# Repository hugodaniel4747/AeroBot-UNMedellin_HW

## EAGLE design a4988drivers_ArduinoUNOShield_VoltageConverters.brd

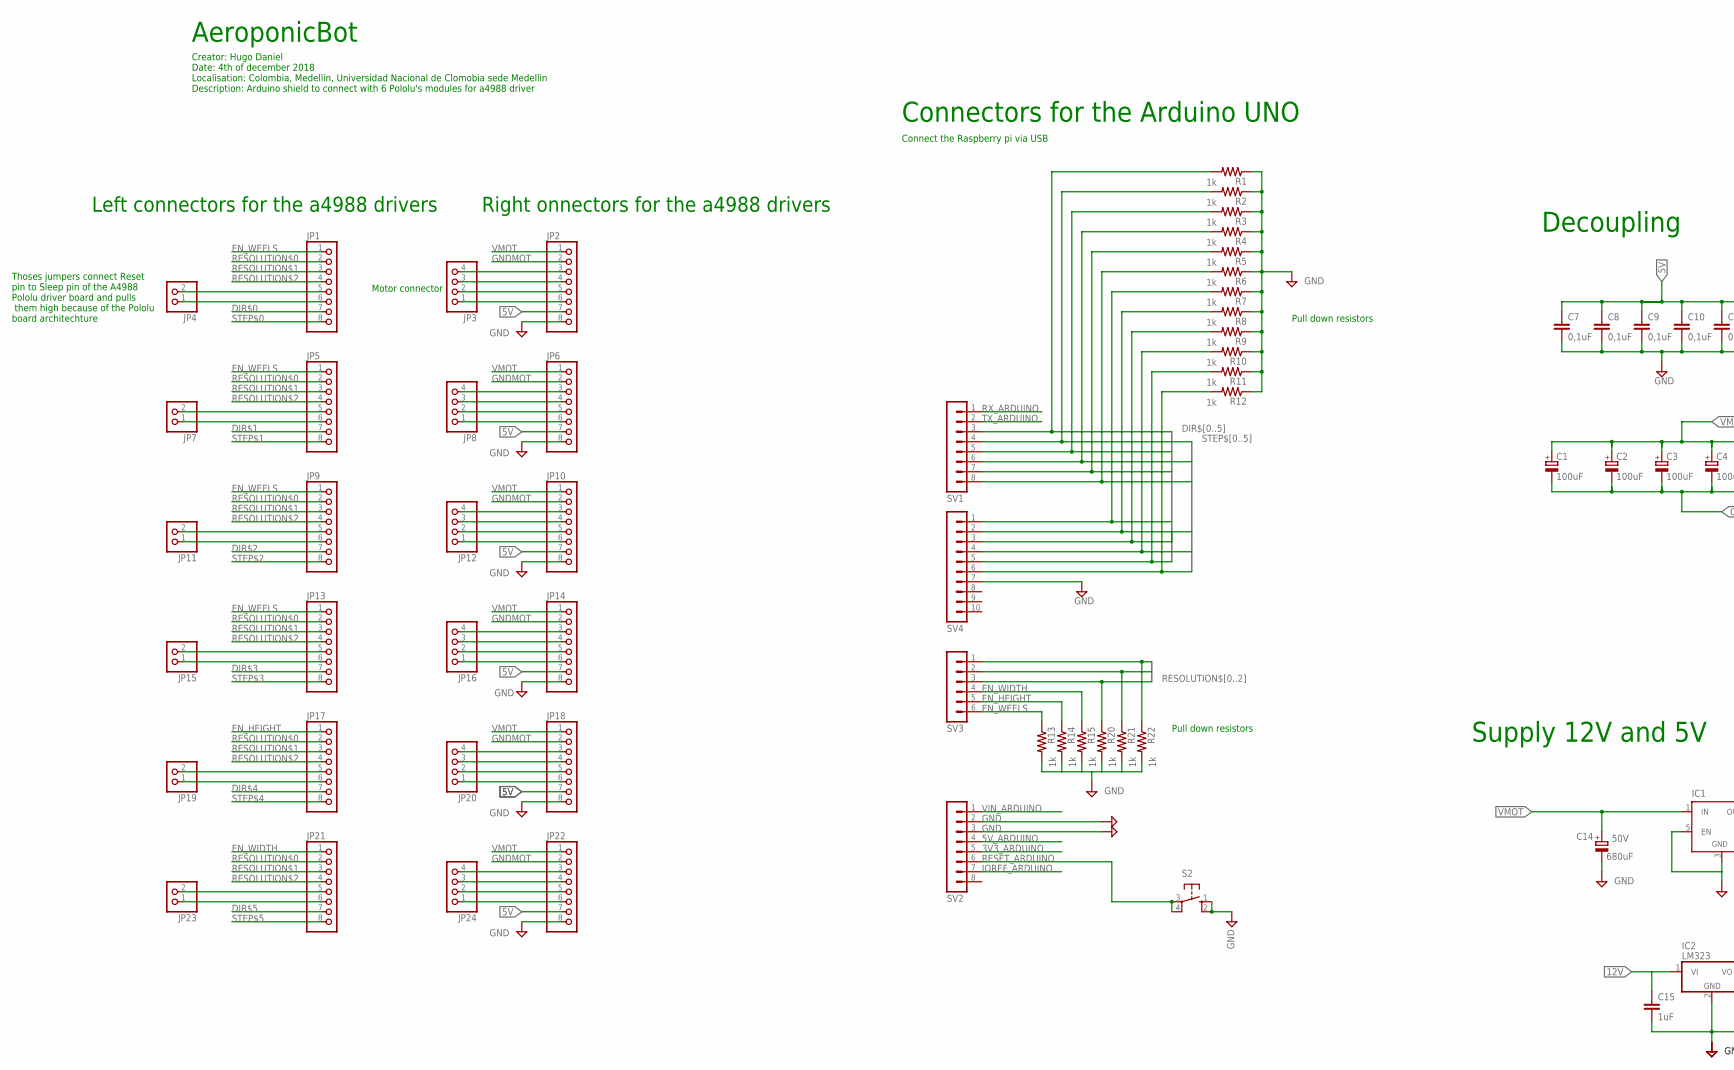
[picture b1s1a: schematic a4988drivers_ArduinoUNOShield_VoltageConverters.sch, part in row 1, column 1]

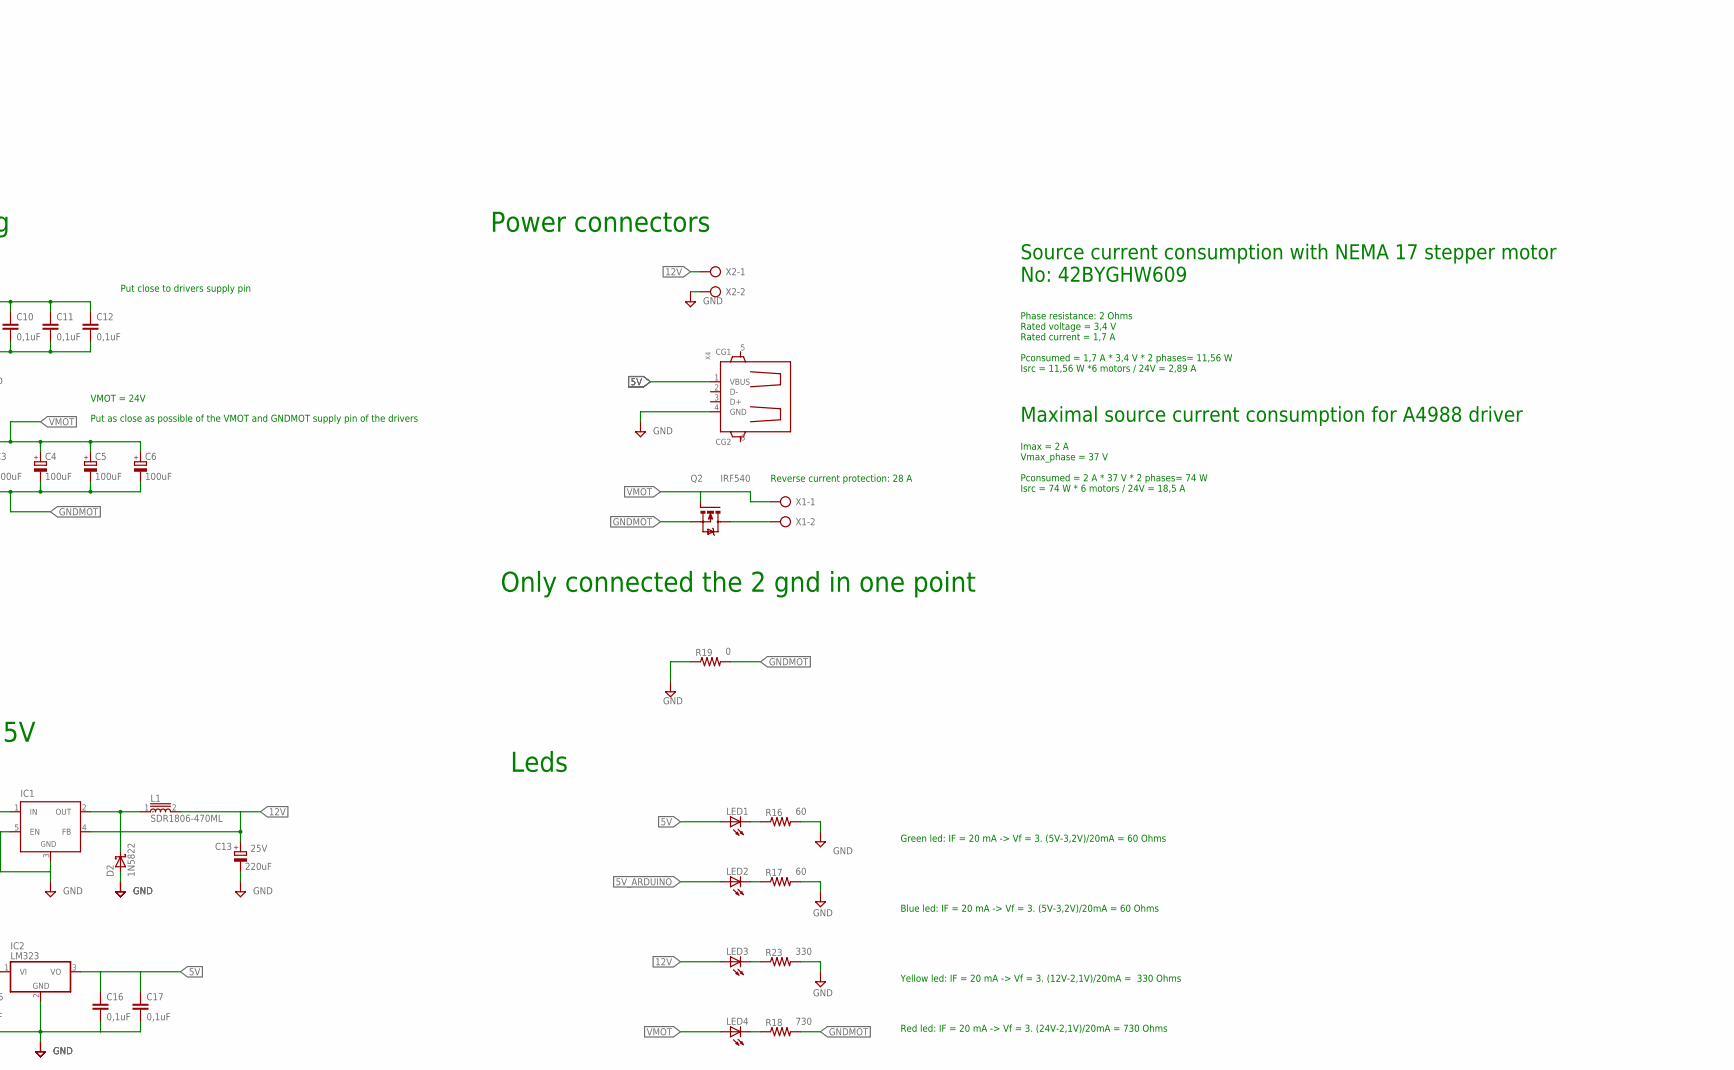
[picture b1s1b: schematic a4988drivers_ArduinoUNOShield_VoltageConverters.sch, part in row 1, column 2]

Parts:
C1, C2, C3, C4, C5, C6: 100uF; E5-10,5
C7, C8, C9, C10, C11, C12, C16, C17: 0,1uF; C050-030X075
C13: 220uF; E5-10,5
C14: 680uF; E5-10,5
C15: 1uF; C050-030X075
D2: 1N5822; DIOAD2120W130L950D530P
IC1: LM2596TV; TO220-51
IC2: LM323; TO220V
JP1, JP2, JP5, JP6, JP9, JP10, JP13, JP14, JP17, JP18, JP21, JP22: PINHD-1X8; 1X08
JP3, JP8, JP12, JP16, JP20, JP24: PINHD-1X4; 1X04
JP4, JP7, JP11, JP15, JP19, JP23: PINHD-1X2; 1X02
L1: SDR1806-470ML; INDP1830X1400X690L250X260N
LED1, LED2, LED3, LED4: LED5MM
Q2: IRF540; TO220BV
R1, R2, R3, R4, R5, R6, R7, R8, R9, R10, R11, R12, R13, R14, R15, R20, R21, R22: 1k; 0207/7
R16, R17: 60; 0207/7
R18: 730; 0207/7
R19: 0; 0207/7
R23: 330; 0207/7
S2: 10-XX; B3F-10XX
SV1, SV2: MA08-1
SV3: MA06-1
SV4: MA10-1
X1, X2: AK500/2
X4: GHI2_USB_HOST_W/CHASSIS_GND; GHI2_USB_HOST_HORIZONTAL_W/CHASSIS_GND

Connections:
3V3_ARDUINO: SV2.5
5V: C7.1, C8.1, C9.1, C10.1, C11.1, C12.1, C16.1, C17.1, IC2.3 (VO), JP2.7, JP6.7, JP10.7, JP14.7, JP18.7, JP22.7, LED1.A, X4.1 (VBUS)
5V_ARDUINO: LED2.A, SV2.4
12V: C13.+, C15.1, IC1.4 (FB), IC2.1 (VI), L1.2, LED3.A, X2.1
DIR$0: JP1.7, R1.2, SV1.3
DIR$1: JP5.7, R3.2, SV1.5
DIR$2: JP9.7, R5.2, SV1.7
DIR$3: JP13.7, R7.2, SV4.1
DIR$4: JP17.7, R9.2, SV4.3
DIR$5: JP21.7, R11.2, SV4.5
EN_HEIGHT: JP17.1, R14.1, SV3.5
EN_WEELS: JP1.1, JP5.1, JP9.1, JP13.1, R13.1, SV3.6
EN_WIDTH: JP21.1, R15.1, SV3.4
GND: C7.2, C8.2, C9.2, C10.2, C11.2, C12.2, C13.-, C14.-, C15.2, C16.2, C17.2, D2.A, IC1.3 (GND), IC1.5 (EN), IC2.2 (GND), JP2.8, JP6.8, JP10.8, JP14.8, JP18.8, JP22.8, R1.1, R2.1, R3.1, R4.1, R5.1, R6.1, R7.1, R8.1, R9.1, R10.1, R11.1, R12.1, R13.2, R14.2, R15.2, R16.2, R17.2, R19.1, R20.2, R21.2, R22.2, R23.2, S2.1 (S), S2.2 (S1), SV2.2, SV2.3, SV4.7, X2.2, X4.4 (GND)
GNDMOT: C1.-, C2.-, C3.-, C4.-, C5.-, C6.-, JP2.2, JP6.2, JP10.2, JP14.2, JP18.2, JP22.2, Q2.S, R19.2
IOREF_ARDUINO: SV2.7
unnamed: D2.C, IC1.2 (OUT), L1.1
unnamed: Q2.D, X1.2
unnamed: LED1.K (C), R16.1
unnamed: JP2.3, JP3.4
unnamed: LED2.K (C), R17.1
unnamed: JP2.4, JP3.3
unnamed: JP2.5, JP3.2
unnamed: JP1.5, JP4.2
unnamed: JP1.6, JP4.1
unnamed: JP2.6, JP3.1
unnamed: JP5.5, JP7.2
unnamed: JP5.6, JP7.1
unnamed: JP6.3, JP8.4
unnamed: JP6.4, JP8.3
unnamed: JP6.5, JP8.2
unnamed: JP6.6, JP8.1
unnamed: JP9.5, JP11.2
unnamed: JP9.6, JP11.1
unnamed: JP10.3, JP12.4
unnamed: JP10.4, JP12.3
unnamed: JP10.5, JP12.2
unnamed: JP10.6, JP12.1
unnamed: JP13.5, JP15.2
unnamed: JP13.6, JP15.1
unnamed: JP14.3, JP16.4
unnamed: JP14.4, JP16.3
unnamed: JP14.5, JP16.2
unnamed: JP14.6, JP16.1
unnamed: JP17.5, JP19.2
unnamed: JP17.6, JP19.1
unnamed: JP18.3, JP20.4
unnamed: JP18.4, JP20.3
unnamed: JP18.5, JP20.2
unnamed: JP18.6, JP20.1
unnamed: JP21.5, JP23.2
unnamed: JP21.6, JP23.1
unnamed: JP22.3, JP24.4
unnamed: JP22.4, JP24.3
unnamed: JP22.5, JP24.2
unnamed: JP22.6, JP24.1
unnamed: LED4.K (C), R18.1
unnamed: LED3.K (C), R23.1
RESET_ARDUINO: S2.3, S2.4 (P1), SV2.6
RESOLUTION$0: JP1.2, JP5.2, JP9.2, JP13.2, JP17.2, JP21.2, R22.1, SV3.1
RESOLUTION$1: JP1.3, JP5.3, JP9.3, JP13.3, JP17.3, JP21.3, R21.1, SV3.2
RESOLUTION$2: JP1.4, JP5.4, JP9.4, JP13.4, JP17.4, JP21.4, R20.1, SV3.3
RX_ARDUINO: SV1.1
STEP$0: JP1.8, R2.2, SV1.4
STEP$1: JP5.8, R4.2, SV1.6
STEP$2: JP9.8, R6.2, SV1.8
STEP$3: JP13.8, R8.2, SV4.2
STEP$4: JP17.8, R10.2, SV4.4
STEP$5: JP21.8, R12.2, SV4.6
TX_ARDUINO: SV1.2
VIN_ARDUINO: SV2.1
VMOT: C1.+, C2.+, C3.+, C4.+, C5.+, C6.+, C14.+, IC1.1 (IN), JP2.1, JP6.1, JP10.1, JP14.1, JP18.1, JP22.1, LED4.A, Q2.G, X1.1

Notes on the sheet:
Put close to drivers supply pin
Only connected the 2 gnd in one point
Connect the Raspberry pi via USB
Put as close as possible of the VMOT and GNDMOT supply pin of the drivers
Left connectors for the a4988 drivers
Connectors for the Arduino UNO
Pull down resistors
Phase resistance: 2 Ohms Rated voltage = 3,4 V Rated current = 1,7 A Pconsumed = 1,7 A * 3,4 V * 2 phases= 11,56 W Isrc = 11,56 W *6 motors / 24V = 2,89 A
Thoses jumpers connect Reset pin to Sleep pin of the A4988 Pololu driver board and pulls them high because of the Pololu board architechture
Motor connector
Right onnectors for the a4988 drivers
Imax = 2 A Vmax_phase = 37 V Pconsumed = 2 A * 37 V * 2 phases= 74 W Isrc = 74 W * 6 motors / 24V = 18,5 A
VMOT = 24V
Source current consumption with NEMA 17 stepper motor No: 42BYGHW609
Maximal source current consumption for A4988 driver
AeroponicBot
Creator: Hugo Daniel Date: 4th of december 2018 Localisation: Colombia, Medellin, Universidad Nacional de Clomobia sede Medellin Description: Arduino shield to connect with 6 Pololu's modules for a4988 driver
Reverse current protection: 28 A
Decoupling
Power connectors
Leds
Supply 12V and 5V
Red led: IF = 20 mA -> Vf = 3. (24V-2,1V)/20mA = 730 Ohms
Yellow led: IF = 20 mA -> Vf = 3. (12V-2,1V)/20mA = 330 Ohms
Blue led: IF = 20 mA -> Vf = 3. (5V-3,2V)/20mA = 60 Ohms
Green led: IF = 20 mA -> Vf = 3. (5V-3,2V)/20mA = 60 Ohms

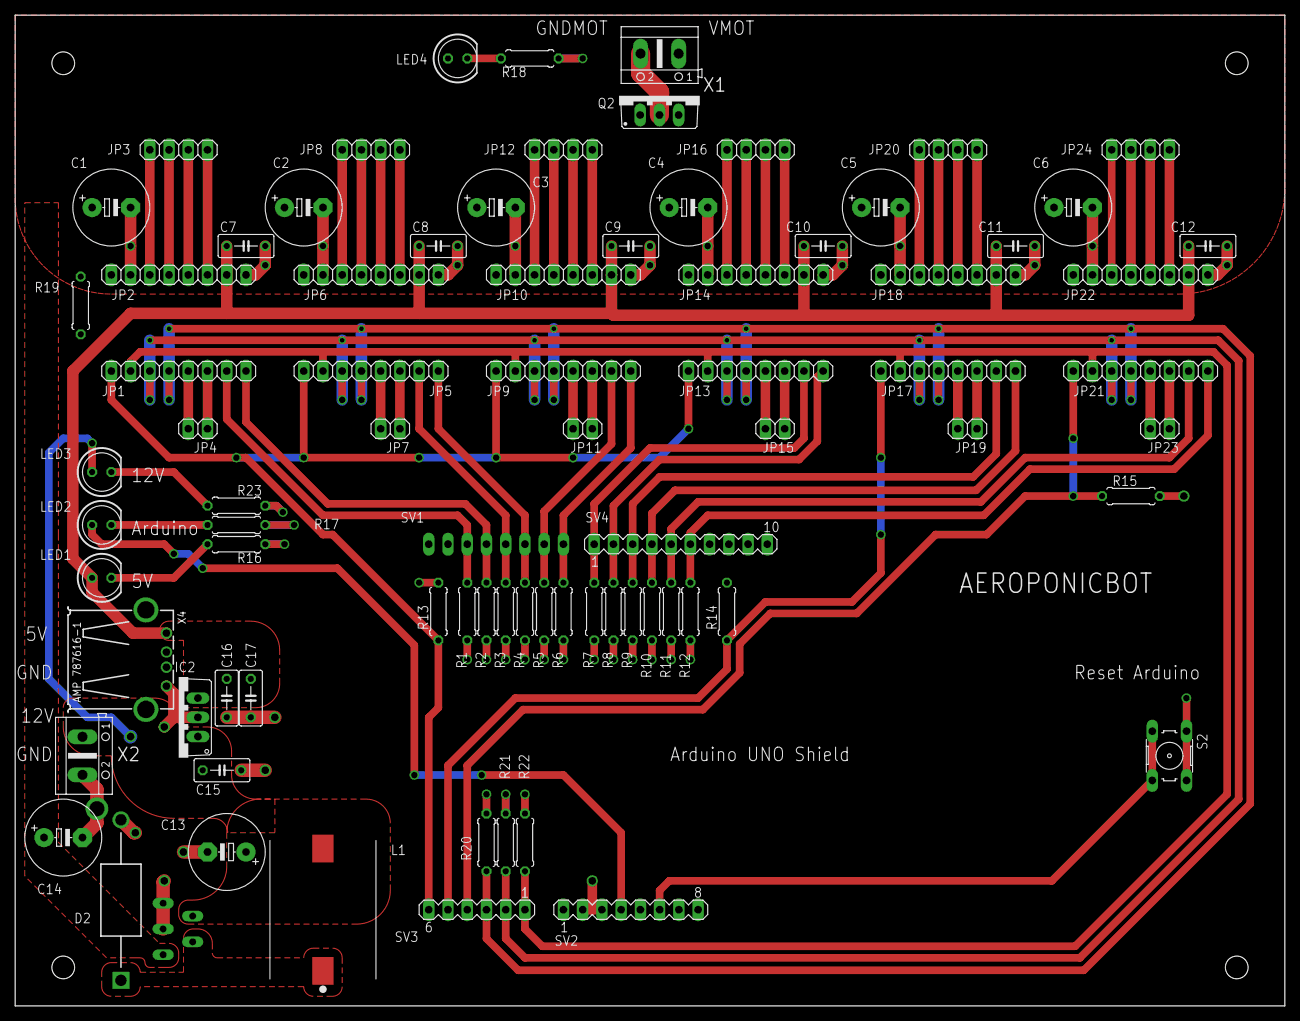
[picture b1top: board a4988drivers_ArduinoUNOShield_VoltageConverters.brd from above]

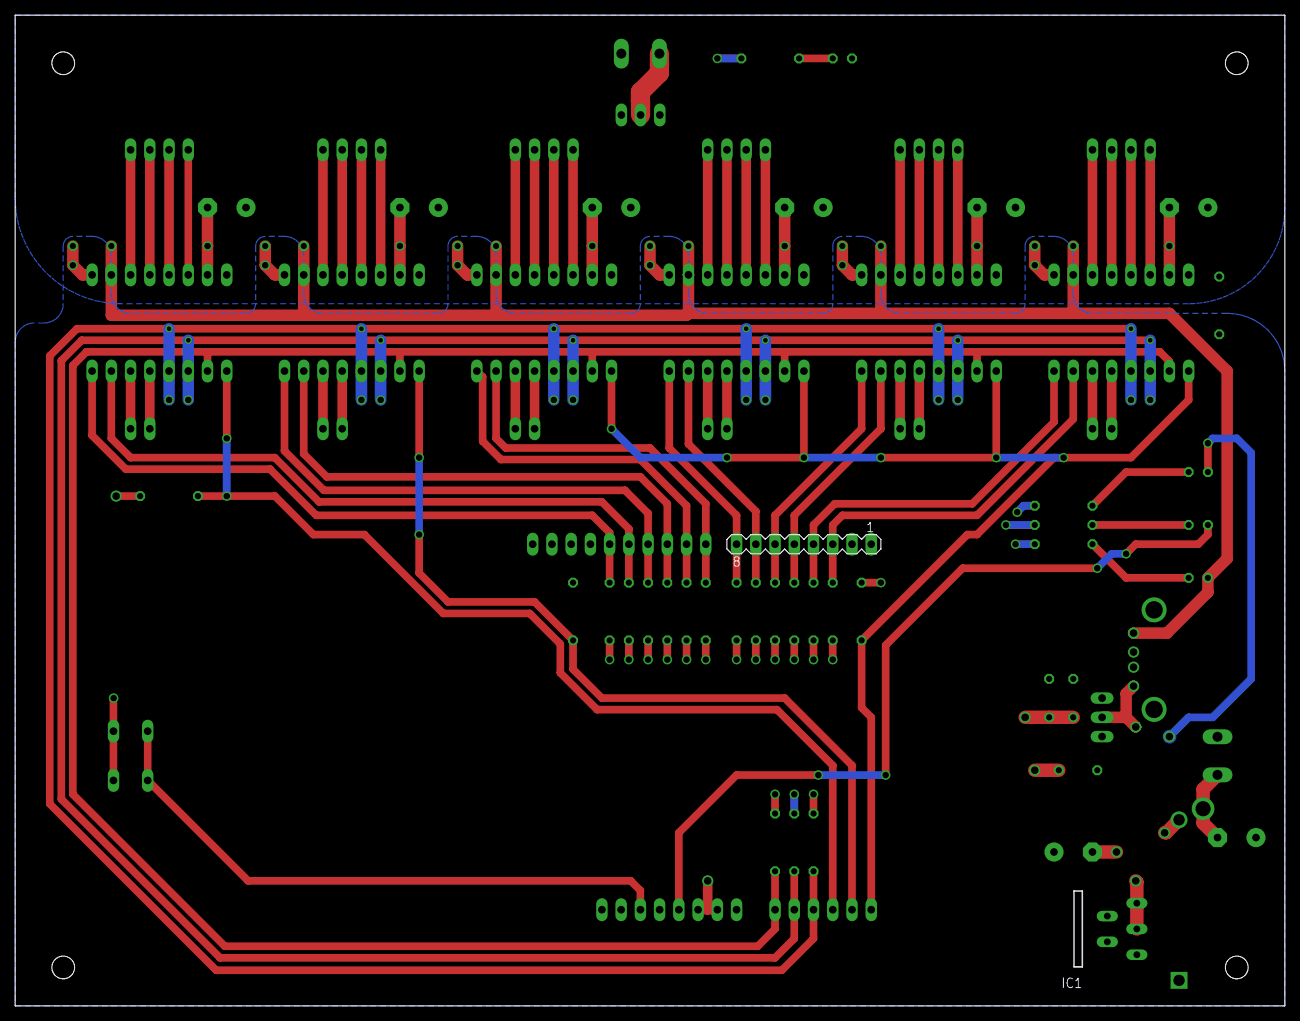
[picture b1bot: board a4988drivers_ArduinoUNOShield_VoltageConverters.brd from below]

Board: 2 copper layers, 167.6 x 130.8 mm, 81 parts (2 on the bottom side), 67 nets.

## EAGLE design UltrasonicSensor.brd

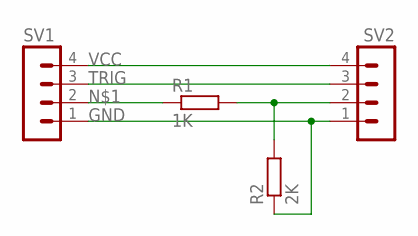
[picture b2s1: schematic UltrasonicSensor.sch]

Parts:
R1: 1K; 0204/7
R2: 2K; 0204/7
SV1, SV2: MA04-1

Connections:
EHO: R1.2, R2.2, SV2.2
GND: R2.1, SV1.1, SV2.1
unnamed: R1.1, SV1.2
TRIG: SV1.3, SV2.3
VCC: SV1.4, SV2.4

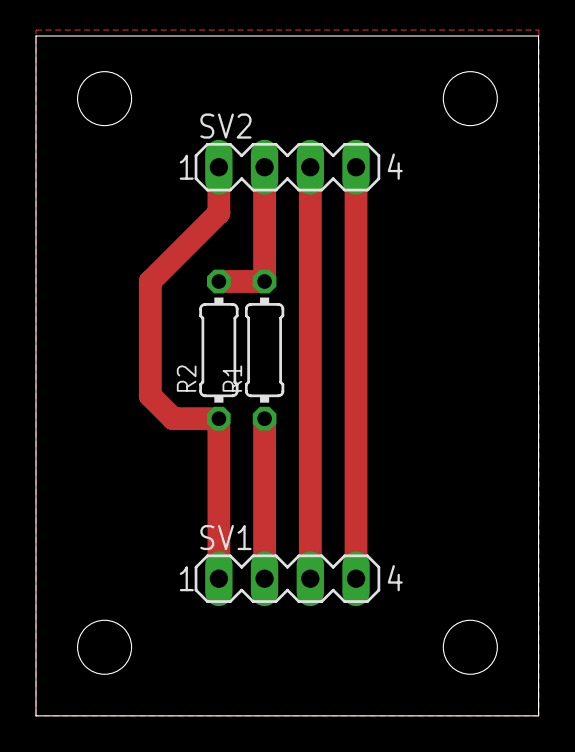
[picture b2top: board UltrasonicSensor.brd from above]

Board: 2 copper layers, 27.9 x 37.8 mm, 4 parts (0 on the bottom side), 5 nets.

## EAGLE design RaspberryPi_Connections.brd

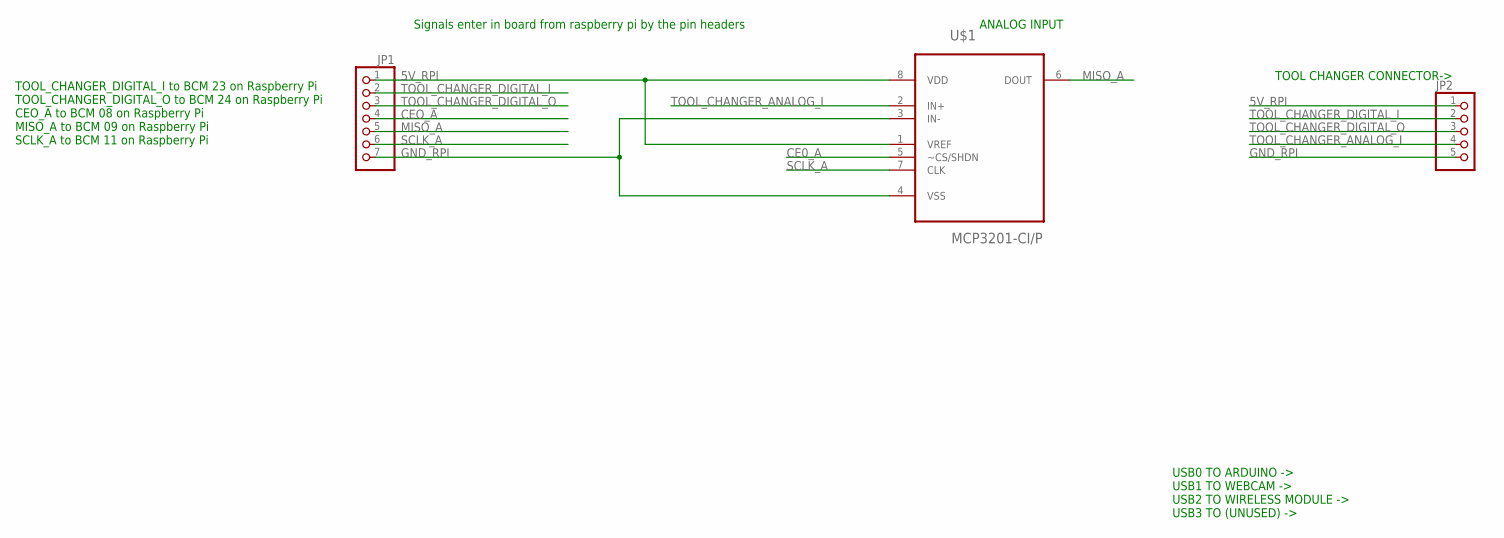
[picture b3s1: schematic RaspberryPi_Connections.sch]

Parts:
JP1: PINHD-1X7; 1X07
JP2: PINHD-1X5; 1X05
U$1: MCP3201-CI/P; DIP254P762X533-8

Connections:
5V_RPI: JP1.1, JP2.1, U$1.1 (VREF), U$1.8 (VDD)
CE0_A: U$1.5 (~CS/SHDN)
CEO_A: JP1.4
GND_RPI: JP1.7, JP2.5, U$1.3 (IN-), U$1.4 (VSS)
MISO_A: JP1.5, U$1.6 (DOUT)
SCLK_A: JP1.6, U$1.7 (CLK)
TOOL_CHANGER_ANALOG_I: JP2.4, U$1.2 (IN+)
TOOL_CHANGER_DIGITAL_I: JP1.2, JP2.2
TOOL_CHANGER_DIGITAL_O: JP1.3, JP2.3

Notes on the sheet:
USB0 TO ARDUINO -> USB1 TO WEBCAM -> USB2 TO WIRELESS MODULE -> USB3 TO (UNUSED) ->
TOOL CHANGER CONNECTOR->
ANALOG INPUT
Signals enter in board from raspberry pi by the pin headers
TOOL_CHANGER_DIGITAL_I to BCM 23 on Raspberry Pi TOOL_CHANGER_DIGITAL_O to BCM 24 on Raspberry Pi CEO_A to BCM 08 on Raspberry Pi MISO_A to BCM 09 on Raspberry Pi SCLK_A to BCM 11 on Raspberry Pi

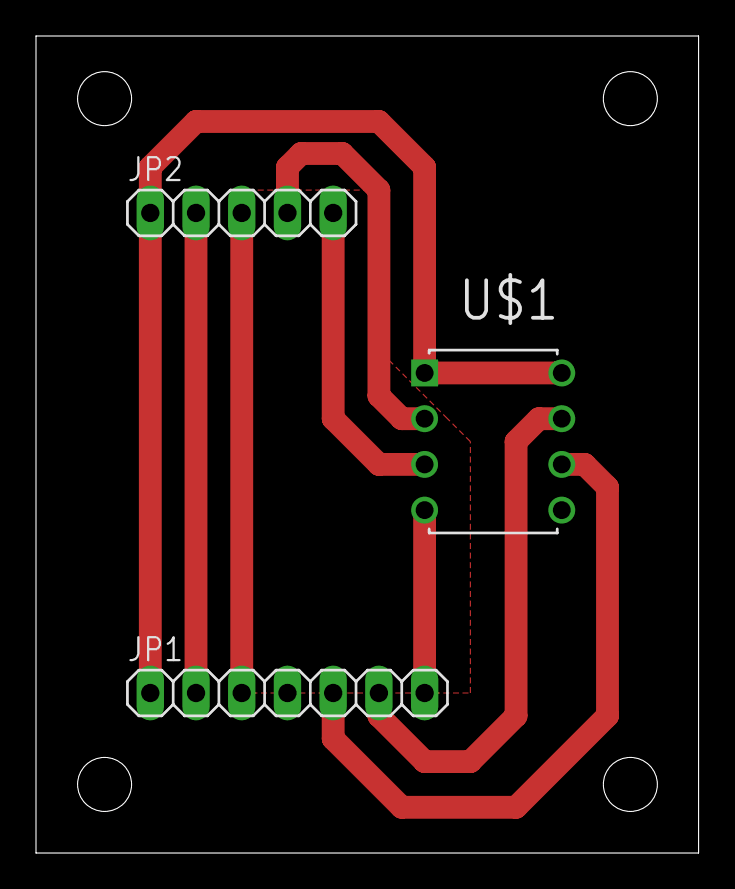
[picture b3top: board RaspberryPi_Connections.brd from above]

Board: 2 copper layers, 36.8 x 45.4 mm, 3 parts (0 on the bottom side), 7 nets.

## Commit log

2018-10-17 Rename Eagle.gitignore to .gitignore
2018-11-14 update board
2018-11-14 Update board with holee for screws
2018-11-15 last commit defore Emmanuels review
2018-11-15 update with new guidlines
2018-11-15 Final update before printing first prototype
2018-12-16 update final from Hugo
